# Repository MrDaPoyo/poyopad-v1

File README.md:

# poyopad-v1
My very very own macropad made in a few hours!

## Overview

This is will be the final look. Quite polished and it has a few inscriptions on the back and the top.

## Schematic

The schematic was overall fun to make. I had to ask @Cyao for a bit of help but other than that, SUPER COOL! 

## PCB Design

I loved arranging the actual PCB. It felt like organizing a desk... Entertaining.

## Case Design

Fusion 360 might've been the hardest part of them all. IT REFUSED TO WORK!!!!1! But in the end everything turned out very well.

## Bill of Materials (BOM)

| Component | Quantity | Description
|-----------|----------|-------------|
| MCU | 1 | XIAO RP2040
| Mechanical Switches | 6 | Default switches provided by Hack Club
| Keycaps | 6 | Standard keycaps
| Diodes | 9 | SK6812MINI |
| PCB | 1 | PCB made by me

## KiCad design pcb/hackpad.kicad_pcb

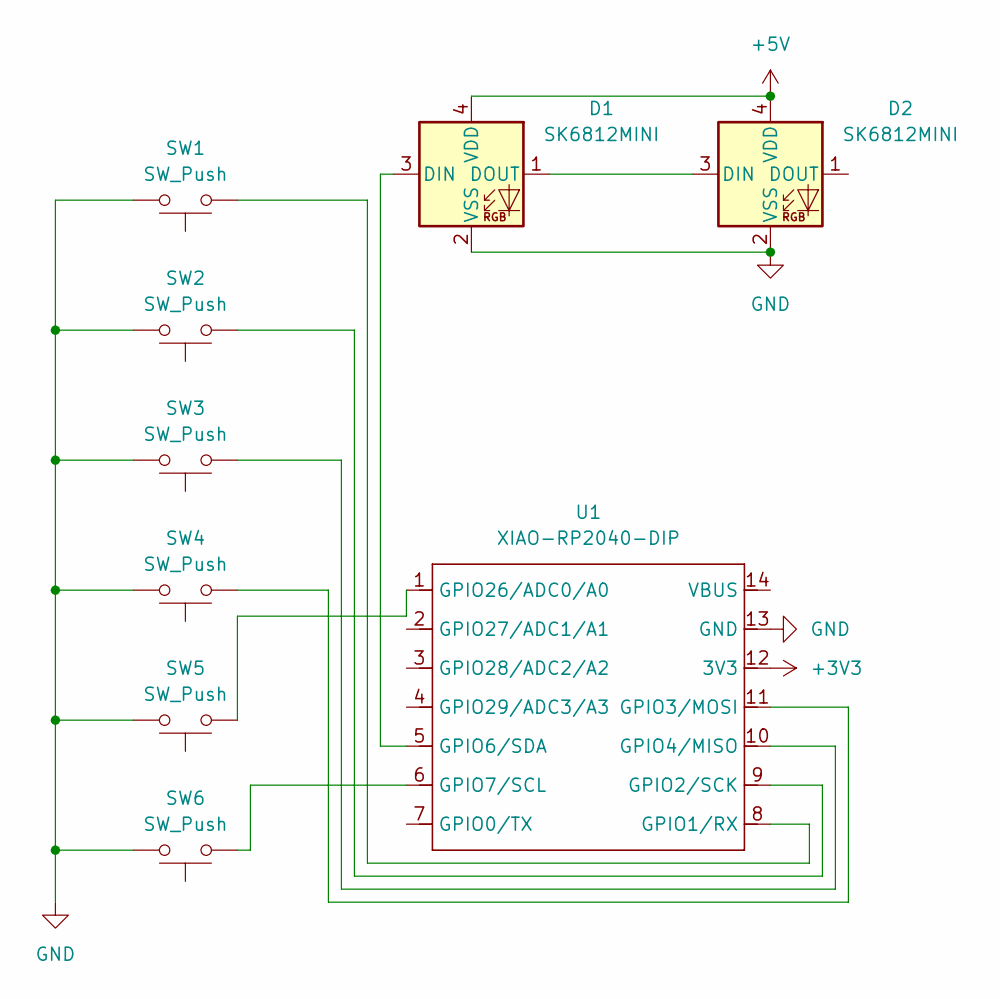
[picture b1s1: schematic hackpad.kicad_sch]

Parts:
D1, D2: SK6812MINI; LED_SK6812MINI_PLCC4_3.5x3.5mm_P1.75mm
SW1, SW2, SW3, SW4, SW5, SW6: SW_Push; SW_Cherry_MX_1.00u_PCB
U1: XIAO-RP2040-DIP

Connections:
+3V3: U1.12 (3V3)
+5V: D1.4 (VDD), D2.4 (VDD)
GND: D1.2 (VSS), D2.2 (VSS), SW1.2, SW2.2, SW3.2, SW4.2, SW5.2, SW6.2, U1.13 (GND)
unnamed: D1.3 (DIN), U1.5 (GPIO6/SDA)
unnamed: D1.1 (DOUT), D2.3 (DIN)
unnamed: SW1.1, U1.8 (GPIO1/RX)
unnamed: SW2.1, U1.9 (GPIO2/SCK)
unnamed: SW4.1, U1.11 (GPIO3/MOSI)
unnamed: SW3.1, U1.10 (GPIO4/MISO)
unnamed: SW6.1, U1.6 (GPIO7/SCL)
unnamed: SW5.1, U1.1 (GPIO26/ADC0/A0)

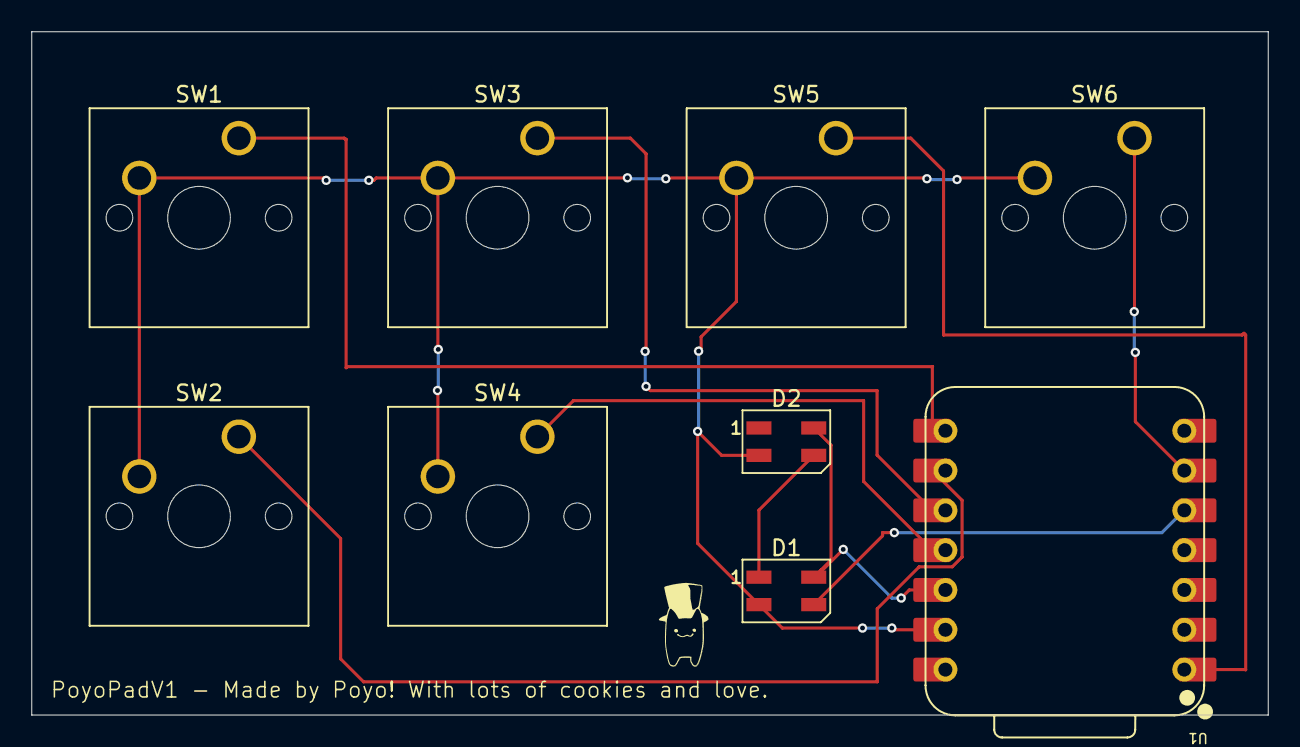
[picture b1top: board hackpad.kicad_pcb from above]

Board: 2 copper layers, 78.9 x 43.6 mm, 10 parts (0 on the bottom side), 10 nets.

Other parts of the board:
Poyo: LOGO

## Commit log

2025-05-20 some parts
2025-05-22 CAD done
2025-05-22 gerber files
2025-05-22 better readme
2025-05-22 YEYYYY FIRMWARE
2025-05-22 new pcb
2025-05-22 readme
